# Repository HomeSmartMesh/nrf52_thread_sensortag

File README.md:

# nrf52_thread_sensortag
nRF52840 small sensor Tag, Low power design, battery operated

# documentation website
https://www.homesmartmesh.com/docs/microcontrollers/nrf52/thread_sensortag/
# community discussion
Free support, feedback and discussions right here on gihub
https://github.com/orgs/HomeSmartMesh/discussions

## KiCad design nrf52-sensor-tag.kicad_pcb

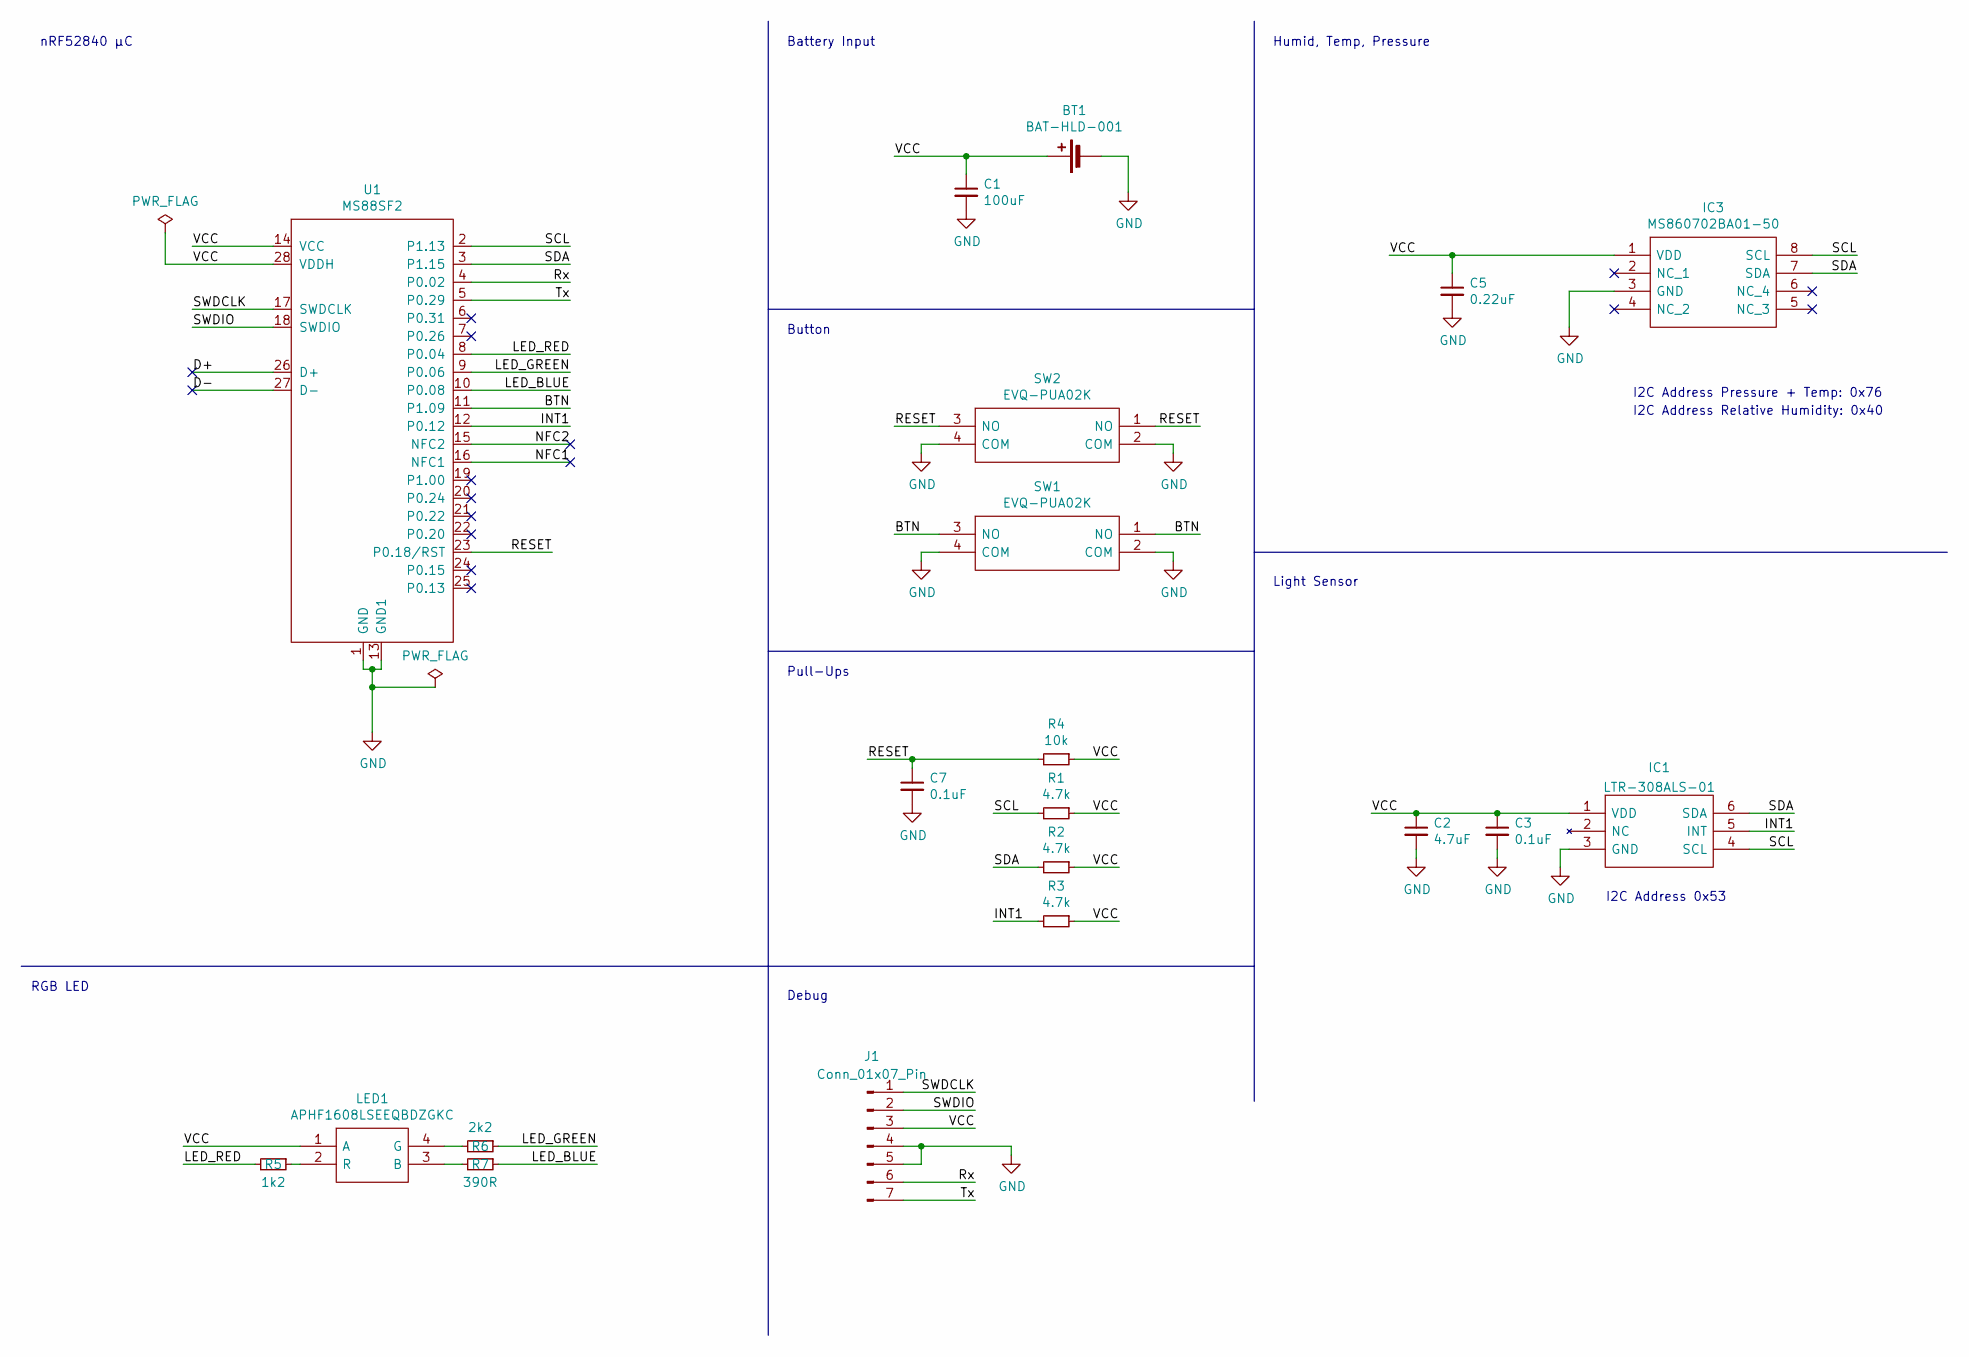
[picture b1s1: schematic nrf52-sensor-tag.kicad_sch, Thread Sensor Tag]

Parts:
BT1: BAT-HLD-001; BATHLD001
C1: 100uF; C_1210_3225Metric
C2: 4.7uF; C_0603_1608Metric
C3, C7: 0.1uF; C_0603_1608Metric
C5: 0.22uF; C_0603_1608Metric
IC1: LTR-308ALS-01; LTR303ALS01; Manufacturer_Part_Number LTR-308ALS-01; Mouser Part Number N/A
IC3: MS860702BA01-50; SON125P300X500X100-8N; Manufacturer_Part_Number MS860702BA01-50; Mouser Part Number 824-MS860702BA01-50
J1: Conn_01x07_Pin; PinSocket_1x07_P2.54mm_Vertical
LED1: APHF1608LSEEQBDZGKC; Manufacturer_Part_Number APHF1608LSEEQBDZGKC; Mouser Part Number 604-APHF1608LQBDZGKC
R1, R2, R3: 4.7k; R_0603_1608Metric
R4: 10k; R_0603_1608Metric
R5: 1k2; R_0603_1608Metric
R6: 2k2; R_0603_1608Metric
R7: 390R; R_0603_1608Metric
SW1, SW2: EVQ-PUA02K; EVQPUA02K; Manufacturer_Part_Number EVQ-PUA02K; Mouser Part Number 667-EVQ-PUA02K
U1: MS88SF2

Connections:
/BTN: SW1.1 (NO), SW1.3 (NO), U1.11 (P1.09)
/D+: U1.26 (D+)
/D-: U1.27 (D-)
/INT1: IC1.5 (INT), R3.2, U1.12 (P0.12)
/LED_BLUE: R7.1, U1.10 (P0.08)
/LED_GREEN: R6.1, U1.9 (P0.06)
/LED_RED: R5.2, U1.8 (P0.04)
/NFC1: U1.16 (NFC1)
/NFC2: U1.15 (NFC2)
/RESET: C7.1, R4.2, SW2.1 (NO), SW2.3 (NO), U1.23 (P0.18/RST)
/Rx: J1.6, U1.4 (P0.02)
/SCL: IC1.4 (SCL), IC3.8 (SCL), R1.2, U1.2 (P1.13)
/SDA: IC1.6 (SDA), IC3.7 (SDA), R2.2, U1.3 (P1.15)
/SWDCLK: J1.1, U1.17 (SWDCLK)
/SWDIO: J1.2, U1.18 (SWDIO)
/Tx: J1.7, U1.5 (P0.29)
/VCC: BT1.1 (+), C1.1, C2.1, C3.1, C5.1, IC1.1 (VDD), IC3.1 (VDD), J1.3, LED1.1 (A), R1.1, R2.1, R3.1, R4.1, U1.14 (VCC), U1.28 (VDDH)
GND: BT1.2 (-), C1.2, C2.2, C3.2, C5.2, C7.2, IC1.3 (GND), IC3.3 (GND), J1.4, J1.5, SW1.2 (COM), SW1.4 (COM), SW2.2 (COM), SW2.4 (COM), U1.1 (GND), U1.13 (GND1)
unnamed: LED1.3 (B), R7.2
unnamed: LED1.4 (G), R6.2
unnamed: LED1.2 (R), R5.1

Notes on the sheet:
Humid, Temp, Pressure
nRF52840 µC
Pull-Ups
RGB LED
Battery Input
I2C Address Pressure + Temp: 0x76
Button
I2C Address 0x53
Debug
I2C Address Relative Humidity: 0x40
Light Sensor

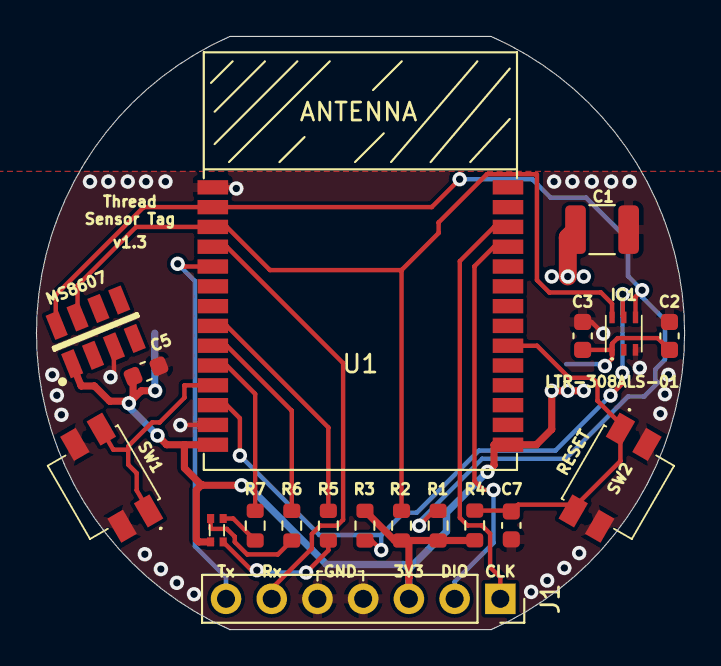
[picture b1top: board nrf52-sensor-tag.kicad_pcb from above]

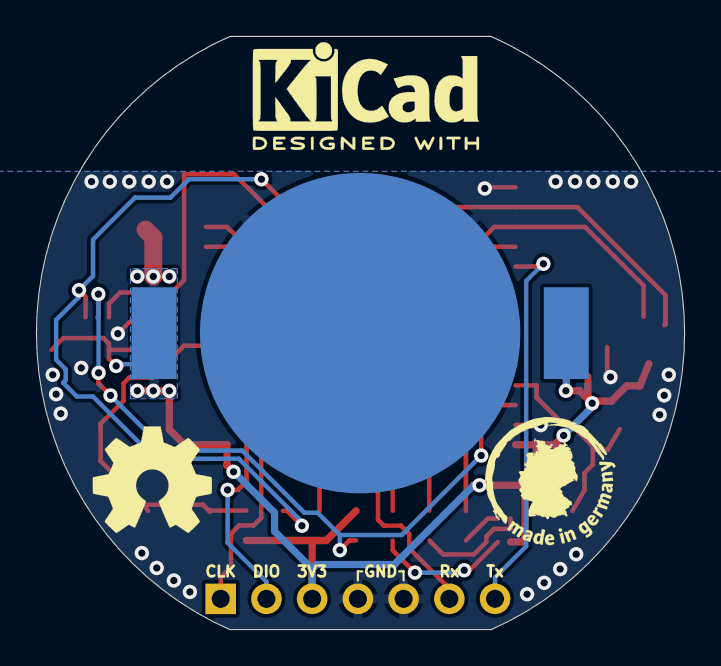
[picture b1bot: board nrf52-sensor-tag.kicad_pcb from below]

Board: 2 copper layers, 36.0 x 33.0 mm, 23 parts (4 on the bottom side), 17 nets.

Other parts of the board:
LOGO1: OSHW-Symbol_6.7x6mm_SilkScreen
LOGO2: LOGO; mig
LOGO3: KiCad-Logo2_5mm_SilkScreen

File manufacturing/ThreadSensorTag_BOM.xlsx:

Reference(s) | Qty | Value | Footprint | DNP | Datasheet | Description | Manufacturer_Name | Manufacturer_Part_Number
BT1 | 1.0 | SMTU2032-LF | BA2032SM:BA2032SM |  | ~ |  | Renata | SMTU2032-LF
C5 | 1.0 | 0.22uF | Capacitor_SMD:C_0603_1608Metric |  | ~
C7, C8 | 2.0 | 0.1uF | Capacitor_SMD:C_0603_1608Metric |  | ~
IC2 | 1.0 | VEML6030 | VEML6030:VEML6030 |  | https://www.vishay.com/docs/84366/veml6030.pdf | VEML6030 Vishay, Ambient Light Sensor, Ambient Light to Digital Data I2C 6-Pin | Vishay | VEML6030
IC3 | 1.0 | MS860702BA01-50 | MS860702BA01-50:SON125P300X500X100-8N |  | https://componentsearchengine.com/Datasheets/1/MS860702BA01-50.pdf | SENSOR SOLUTIONS - TE CONNECTIVITY - MS860702BA01-50 - PRESSURE SENSOR, 10MBAR-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 | TE Connectivity | MS860702BA01-50
J3 | 1.0 | DNP | Connector_PinHeader_2.54mm:PinHeader_1x07_P2.54mm_Vertical | DNP | ~
LED1 | 1.0 | APHF1608LSEEQBDZGKC | APHF1608LSEEQBDZGKC:APHF1608LSEEQBDZGKC |  | https://componentsearchengine.com/Datasheets/1/APHF1608LSEEQ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 | Standard LEDs - SMD RGB 0603 SMD | Kingbright | APHF1608LSEEQBDZGKC
R1, R2 | 2.0 | 4.7k | Resistor_SMD:R_0603_1608Metric |  | ~
R3, R4 | 2.0 | 10k | Resistor_SMD:R_0603_1608Metric |  | ~
R5 | 1.0 | 1k2 | Resistor_SMD:R_0603_1608Metric |  | ~
R6 | 1.0 | 2k2 | Resistor_SMD:R_0603_1608Metric |  | ~
R7 | 1.0 | 390R | Resistor_SMD:R_0603_1608Metric |  | ~
SW1, SW2 | 2.0 | EVQ-PUA02K | EVQ-PUA02K:EVQPUA02K |  | https://www.mouser.in/ProductDetail/Panasonic/EVQ-PUA02K?qs=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 | Tactile Switches SIDE PUSH 2.2NF 4.7x3.2x1.65mm | Panasonic | EVQ-PUA02K
U1 | 1.0 | MS88SF2 | MS88SF2:MS88SF2 |  | https://www.minew.com/products/nrf52840-module-ms88sf2.html |  | Minew | MS88SF2

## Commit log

2021-02-07 First implementation and size check
2021-02-07 Moved components and routed the board
2021-02-07 Attached the sensors VCC to GPIOs of the nrf instead vcc (incl. a jumper just in case)
2021-02-07 Add debug connector
2021-02-08 Beautify schematics + added debug connector
2021-02-08 Finalized layout
2021-02-08 Fix button orientation
2021-02-09 takeover sleepy publisher 1st commit as is
2021-02-09 built example with env var
2021-02-09 Add new alternative sensors
2021-02-09 Add MS88SF2 nRF52 Module and re-arranged components
2021-02-10 Add 3D Model for MS88SF1
2021-02-10 Add Gerbers and BOM to manufacturing folder
2021-02-10 added ozone debugging
2021-02-13 successfully running Thread to MQTT
2021-02-14 Removed unneseccary components because the battery is a very undisturbed source
2021-02-14 added zephyr blink example
2021-02-16 leds running with dongle dts
2021-03-04 renamed directory
2021-03-04 log running
2021-03-04 cleaned up RTT logging
2021-03-06 added rtt shell config
2021-03-15 failing device get null
2021-03-15 sensor device not found
2021-03-17 first twi integration for max44009 sensor
2021-03-26 added discord and ongoing sensor
2021-03-26 missing inamge
2021-04-04 Add RGB LED
2021-04-04 Fix DRC errors
2021-04-04 Add Gerber files plot
2021-04-10 initial print log
2021-04-10 successfully running RTT
2021-04-11 first board and dts version
2021-04-11 corrected dts error and pushed boards on top
2021-04-12 renamed firmware directories
2021-04-12 running user button callback
2021-04-12 turned log into shell
2021-04-12 building Thread
2021-04-12 samples plan
2021-04-13 thread log
2021-04-15 thread config and mqttsn
2021-04-15 #4 Sensor Tag improvements suggestions
    https://github.com/HomeSmartMesh/nrf52_thread_sensortag/issues/4
2021-04-15 Generated BOM and Gerbers for v1.1
2021-04-15 Add i2c example (failed for 0x40 and 0x76)
2021-04-16 preparing for i2c
2021-04-17 pinging all i2c sensors
2021-04-17 added separate config for log and shell
2021-04-17 compiling with MAX44009 mock
2021-04-17 updating for veml light sensor
2021-04-17 log vishay no sensor
2021-04-17 finding device fetch fails
2021-06-07 New edge cut + sensor turned by 68°
2021-06-07 Generated html BOM
2021-06-07 Generated Gerber files
2021-07-13 updated forum link
2021-08-25 Added Open Source Hardware Logo + Made in Germany + Designed with KiCad
2021-08-28 Add new battery holder component
2021-08-28 Rerouting using new Battery Holder (autorouted)
2021-08-29 Finalized schematics + generated manufacturing files
2021-09-02 Add 100uF cap + regenerated gerbers incl. F+B_Paste
2022-09-13 Replaced light sensor VEML6030 with LTR-308ALS-01
2023-09-02 Added github action to create manufacturing files
2023-09-02 Moved action into its folder workflows
2023-09-02 Port from KiCad 5 to KiCad 6
2023-09-02 Added verbose log output
2023-09-02 Try to fix KiCad Version issue
2023-09-02 Add even more debug log
2023-09-03 Removed old kicad file
2023-09-03 Fix DRC violations with KiCad 7
2023-09-03 Change KiBot action pcb_print to pcbdraw
2023-09-03 Ignore DRC library violation
2024-05-08 Add enclosure STL files

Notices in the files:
nrf52-sensor-tag.kicad_sch:
Licence: MIT
